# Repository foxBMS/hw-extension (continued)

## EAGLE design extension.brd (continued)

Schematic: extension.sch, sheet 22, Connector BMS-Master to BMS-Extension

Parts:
JP2201, JP2202: PINHD-2X12; 2X12

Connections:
+3.3V_0: JP2201.1, JP2201.3, JP2202.1, JP2202.3; also elsewhere on the board
ADC_MCU_0_CH_0: JP2202.8; also elsewhere on the board
ADC_MCU_0_CH_1: JP2202.7; also elsewhere on the board
ADC_MCU_0_CH_2: JP2202.6; also elsewhere on the board
ADC_MCU_0_CH_3: JP2202.5; also elsewhere on the board
ADC_MCU_0_CH_4: JP2202.9; also elsewhere on the board
CAN_1_RX: JP2201.6; also elsewhere on the board
CAN_1_TRANS_STANDBY_CONTROL: JP2201.5; also elsewhere on the board
CAN_1_TX: JP2201.7; also elsewhere on the board
CONTACTOR_6_CONTROL: JP2201.18; also elsewhere on the board
CONTACTOR_6_FEEDBACK: JP2201.17; also elsewhere on the board
CONTACTOR_7_CONTROL: JP2201.16; also elsewhere on the board
CONTACTOR_7_FEEDBACK: JP2201.15; also elsewhere on the board
CONTACTOR_8_CONTROL: JP2202.10; also elsewhere on the board
CONTACTOR_8_FEEDBACK: JP2202.11; also elsewhere on the board
DATA_STORAGE_SPI_MISO: JP2201.21; also elsewhere on the board
DATA_STORAGE_SPI_MOSI: JP2201.19; also elsewhere on the board
DATA_STORAGE_SPI_SCK: JP2201.20; also elsewhere on the board
DATA_STORAGE_SPI_SDCARD_NSS: JP2201.23; also elsewhere on the board
GND_0: JP2201.2, JP2201.4, JP2202.2, JP2202.4; also elsewhere on the board
ISONOC_0_CONTROL: JP2202.16; also elsewhere on the board
ISONOC_1_CONTROL: JP2202.17; also elsewhere on the board
ISONOC_2_CONTROL: JP2202.18; also elsewhere on the board
ISONOC_3_CONTROL: JP2202.19; also elsewhere on the board
ISONOC_4_CONTROL: JP2202.20; also elsewhere on the board
ISONOC_5_CONTROL: JP2202.21; also elsewhere on the board
ISO_GPIO_MCU_0_IN_0: JP2202.22; also elsewhere on the board
ISO_GPIO_MCU_0_IN_1: JP2202.23; also elsewhere on the board
ISO_GPIO_MCU_0_IN_2: JP2201.13; also elsewhere on the board
ISO_GPIO_MCU_0_IN_3: JP2201.10; also elsewhere on the board
ISO_GPIO_MCU_0_OUT_0: JP2201.9; also elsewhere on the board
ISO_GPIO_MCU_0_OUT_1: JP2201.14; also elsewhere on the board
ISO_GPIO_MCU_0_OUT_2: JP2201.11; also elsewhere on the board
ISO_GPIO_MCU_0_OUT_3: JP2201.12; also elsewhere on the board
RS485_MCU_0_DE: JP2202.15; also elsewhere on the board
RS485_MCU_0_NRE: JP2202.14; also elsewhere on the board
RS485_MCU_0_RX: JP2202.13; also elsewhere on the board
RS485_MCU_0_TX: JP2202.12; also elsewhere on the board
SDCARD_SUPPLY_CONTROL: JP2201.22; also elsewhere on the board

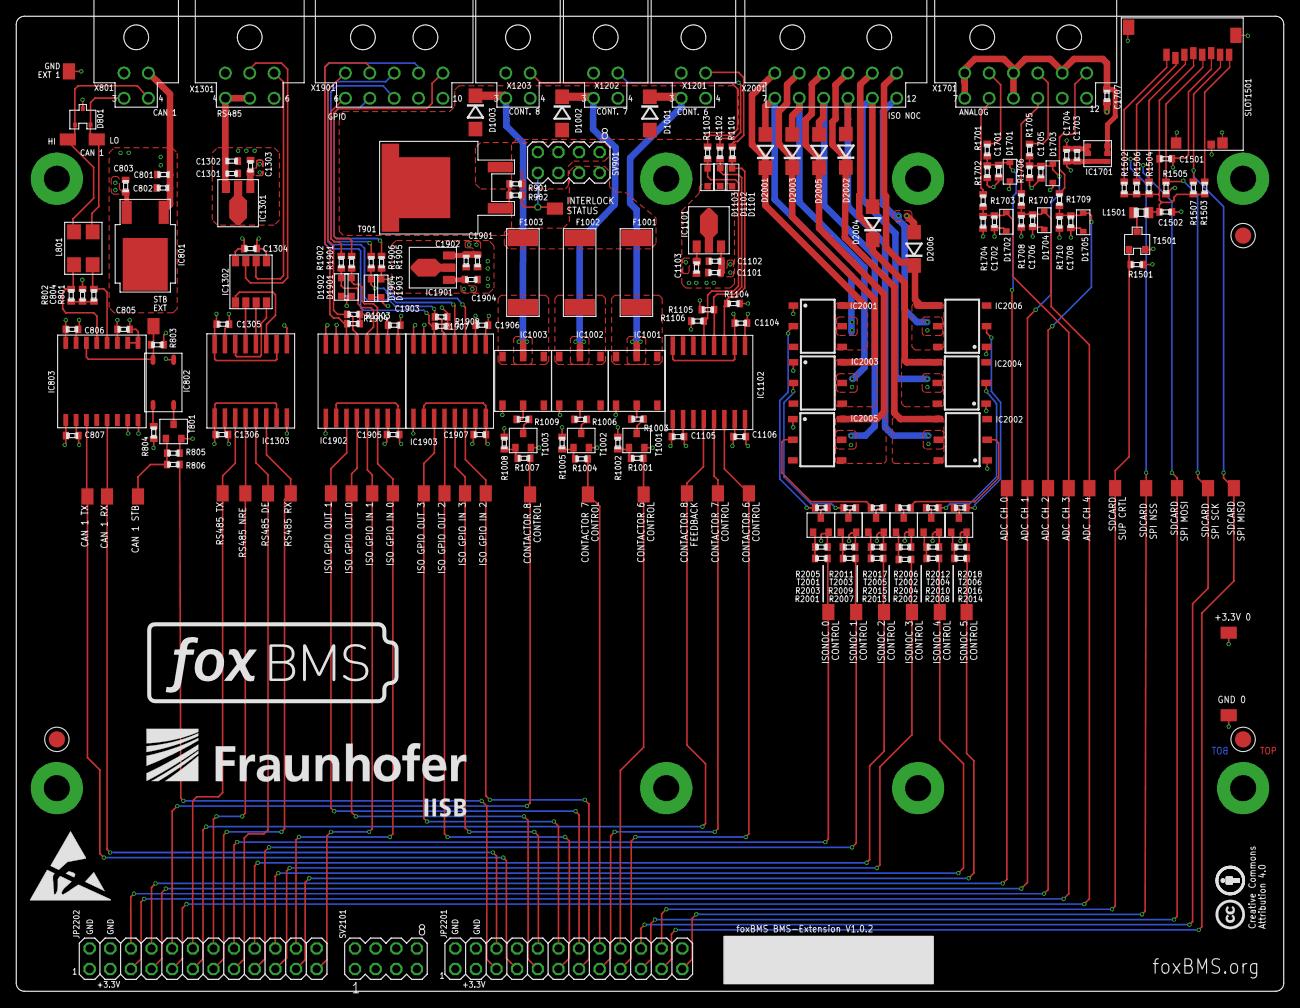
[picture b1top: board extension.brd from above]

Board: 4 copper layers, 156.0 x 120.0 mm, 223 parts (0 on the bottom side), 141 nets.

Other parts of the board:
U$1: ESD_10.00
U$2, U$3, U$4: FIDUCIAL_1MM

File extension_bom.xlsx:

Populate | Qty | Value | Device | Package | Parts | Description | Farnell | Digikey | Mouser
 | Resistor
yes | 5 | 0 | R_MET_0603 | 0603 | R1701 R1703 R1705 R1707 R1709 | Resistor | 2059527
yes | 11 | 10 | R_MET_0603 | 0603 | R902 R1001 R1004 R1007 R2001 R2002 R2007 R2008 R2013 R2014 R806 | Resistor | 2302958
yes | 25 | 10k | R_MET_0603 | 0603 | R901 R1002 R1005 R1008 R1104 R1105 R1106 R1502 R1503 R1504 R1505 R1506 R1507 R1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 | Resistor | 2303192
yes | 5 | 4.75k | R_MET_0603 | 0603 | R1702 R1704 R1706 R1708 R1710 | Resistor | 2094611
yes | 10 | 430 | R_MET_0603 | 0603 | R1003 R1006 R1009 R2005 R2006 R2011 R2012 R2017 R2018 R804 | Resistor | 2145386
yes | 1 | 47k | R_MET_0603 | 0603 | R1501 | Resistor | 2303213
yes | 7 | 47 | R_MET_0603 | 0603 | R1101 R1102 R1103 R1901 R1902 R1905 R1906 | Resistor | 2145397
yes | 2 | 62 | R_MET_0603 | 0603 | R801 R802 | Resistor | 2303039
 | Capacitor
yes | 4 | 100n 50V | C_NP0_0603 | 0603 | C1901 C802 C1101 C1302 | Capacitor | 2346967
yes | 26 | 100n | C_X7R_0603 | 0603 | C803 C804 C805 C806 C807 C1103 C1104 C1105 C1106 C1303 C1304 C1305 C1306 C1701 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 | Capacitor | 1828890
yes | 3 | 1µ | C_X7R_0603 | 0603 | C1703 C1902 C1502 | Capacitor | 1907343
yes | 3 | 1µ 35V | C_X7R_0603 | 0603 | C801 C1102 C1301 | Capacitor | 2346909
 | Testpad
no | 44 | PAD_2.0X1.5MM | PAD_2.0X1.5MM | PAD2.0X1.5MM | LSP801 LSP802 LSP803 LSP804 LSP805 LSP806 LSP807 LSP901 LSP1001 LSP1002 LSP1003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 | Testpoint |  | 952-2664-1-ND
 | L
yes | 1 |  | B82789N | B82789*N | L801 |  |  |  | 871-B82789C513N2
yes | 1 | 22u | L1210 | L1210 | L1501 |  | 2443249
 | Diode
yes | 5 | MM3Z3V3ST1G | MM3Z_XVX_T1 | SOD323 | D1701 D1702 D1703 D1704 D1705 | MM3Z_xVx_T1 Series Zener Diode |  | MM3Z3V3ST1GOSCT-ND
yes | 7 | CDSOD323-T05 | CDSOD323-T05 | SOD323 | D1101 D1102 D1103 D1901 D1902 D1903 D1904 | TVS CDSOD323-T05 | 2341914
yes | 1 | PESD1CAN | PESD1CAN | SOT-23_NEU | D801 | NXP PESD1CAN CAN bus ESD protection diode | 1510703
no | 9 |  | DIODE-DO214BA | DO214BA | D1001 D1002 D1003 D2001 D2002 D2003 D2004 D2005 D2006 | DIODE | 1467477
 | Transistor
yes | 1 | BSS84P | BSS84P | SOT23 | T1501 | #2245 | 1056526
yes | 1 | BUK964R8-60E | BUK964R8-60E | TO-263AB | T901 | #2797 N-Channel PowerTrench MOSFET 60V, 75A 10.5mOhm | 2254205
yes | 10 | IRLML0100TRPBF | IRLML0100TRPBF | SOT-23 | T801 T1001 T1002 T1003 T2001 T2002 T2003 T2004 T2005 T2006 |  | 1783928
 | IC
yes | 1 | ADR3425ARJZ | ADR3425ARJZ | SOT23-6 | IC1701 | Micropower, high accuracy, voltage references | 2377039
yes | 1 | ADUM3300 | ADUM3300 | SO-16W | IC1102 | Triple-Channel Digital Isolators | 2409432
yes | 1 | ADUM3401 | ADUM3401 | SO16W | IC1303 | Analog Devices Magnetkoppler 4-Kanal | 1274129
yes | 2 | ADUM3402 | ADUM3402 | SO16W | IC1902 IC1903 | Analog Devices Magnetkoppler 4-Kanal | 1274127
yes | 1 | LT1785CS8#PBF | LT1785CS8#PBF | SOIC8 | IC1302 | Low Power RS485 Interface Transceiver | 1663498
yes | 1 | TJA1052IT/5Y | TJA1052IT/5Y | SO16W | IC803 |  | 2400552
 | Opto
yes | 9 | AQV252G2SX | AQV252G2SX | SOP06 | IC1001 IC1002 IC1003 IC2001 IC2002 IC2003 IC2004 IC2005 IC2006 |  |  | 255-3594-1-ND
yes | 1 | CPC1008N | CPC1008N | SOP4 | IC802 | CLARE - Single-Pol, Normally Open 4-Pin SOP OptoMOS Relay, 150mA load current | 1653755
 | Regulator
yes | 1 | KA7805ERT | KA7805ERT | TO252 | IC801 | Positive VOLTAGE REGULATOR | 2102585
yes | 3 | UA78L05CPK | UA78L05CPK | SOT89 | IC1101 IC1301 IC1901 | POSITOIV-VOLTAGE REGULATORS | 2112604
 | Misc
yes | 1 |  | 47352-1001 | 47352-1001 | SD-Micro SLOT |  | 2424133
yes | 3 | 4,0A_UMT | 4,0MA_UMT | F_SMD_11,00MMX3,00MMX3,00MM_(UMT)_R_SCHURTER_REV01 | F1001 F1002 F1003 | UMT-Serie - Schurter Electronic Components |  | 486-1253-ND | 693-3403.0172.11
 | Connector THD
yes | 1 |  | HEADER_POS10_43045-1000 | 43045-1000 | X1901 | Molex - Micro-Fit 3.0 Series connector, 3.00mm (0.118) pitch header, 10 positio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 | 1012255
yes | 2 |  | HEADER_POS12_43045-1200 | 43045-1200 | X1701 X2001 | Molex - Micro-Fit 3.0 Series connector, 3.00mm (0.118) pitch header, 12 positio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 | 9732977
yes | 4 |  | HEADER_POS4_43045-0400 | 43045-0400 | X801 X1201 X1202 X1203 | Molex - Micro-Fit 3.0 Series connector, 3.00mm (0.118) pitch header, 4 position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 | 9733019
yes | 1 |  | HEADER_POS6_43045-0600 | 43045-0600 | X1301 | Molex - Micro-Fit 3.0 Series connector, 3.00mm (0.118) pitch header, 6 position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 | 1012252
yes | 1 |  | MA04-2 | MA04-2 | SV901 | PIN HEADER |  | SAM1096-04-ND
no | 1 |  |  |  | SV2101 |  | 2025250
yes | 2 |  | PINHD-2X12 | 2X12 | JP2201 JP2202 | PIN HEADER |  | SAM1096-12-ND

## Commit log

2017-12-13 Intial commit of the hardware design resources for the foxBMS Extension board
2017-12-13 fixed fuse value in schematic
2017-12-13 fixed README.md

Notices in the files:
extension.brd:
Creative Commons
Attribution 4.0
parts and their libraries:
foxBMS_BMS-Master_V1.00_A: LICENSE: Creative Commons Attribution 4.0
